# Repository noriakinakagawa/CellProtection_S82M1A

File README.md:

# CellProtection_S82M1A
1セル用バッテリー保護IC S-82M1Aテスト基板のKiCAD 6.0データ。

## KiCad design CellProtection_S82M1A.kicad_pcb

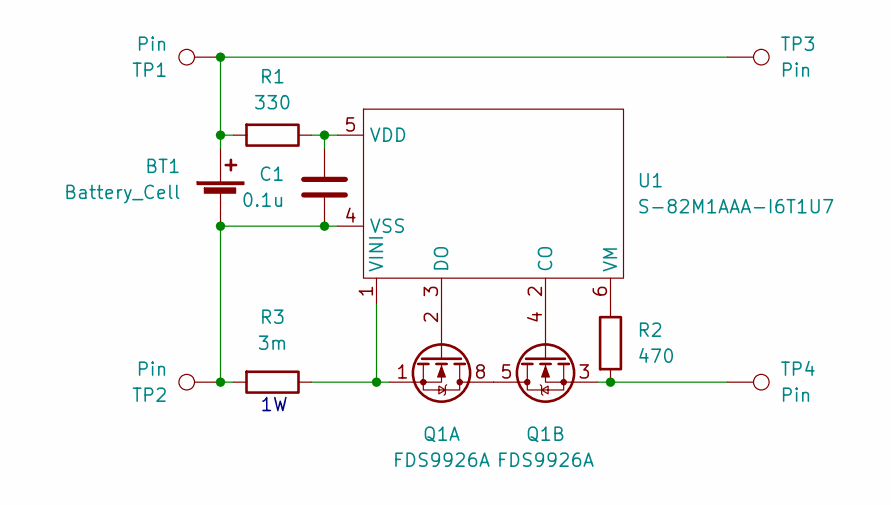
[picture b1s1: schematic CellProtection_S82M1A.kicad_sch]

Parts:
BT1: Battery_Cell; 1043
C1: 0.1u; C_0603_1608Metric_Pad1.08x0.95mm_HandSolder
Q1: FDS9926A; SOIC-8_3.9x4.9mm_P1.27mm
R1: 330; R_0603_1608Metric_Pad0.98x0.95mm_HandSolder
R2: 470; R_0603_1608Metric_Pad0.98x0.95mm_HandSolder
R3: 3m; R_1210_3225Metric_Pad1.30x2.65mm_HandSolder
TP1, TP2, TP3, TP4: Pin; TestPoint_THTPad_1.5x1.5mm_Drill0.7mm
U1: S-82M1AAA-I6T1U7; S-82M1A

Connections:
unnamed: BT1.1 (+), R1.2, TP1.1, TP3.1
unnamed: BT1.2 (-), C1.2, R3.2, TP2.1, U1.4 (VSS)
unnamed: C1.1, R1.1, U1.5 (VDD)
unnamed: Q1.1 (S1), R3.1, U1.1 (VINI)
unnamed: Q1.2 (G1), U1.3 (DO)
unnamed: Q1.3 (S2), R2.2, TP4.1
unnamed: Q1.4 (G2), U1.2 (CO)
unnamed: Q1.5 (D2), Q1.6 (D2), Q1.7 (D1), Q1.8 (D1)
unnamed: R2.1, U1.6 (VM)

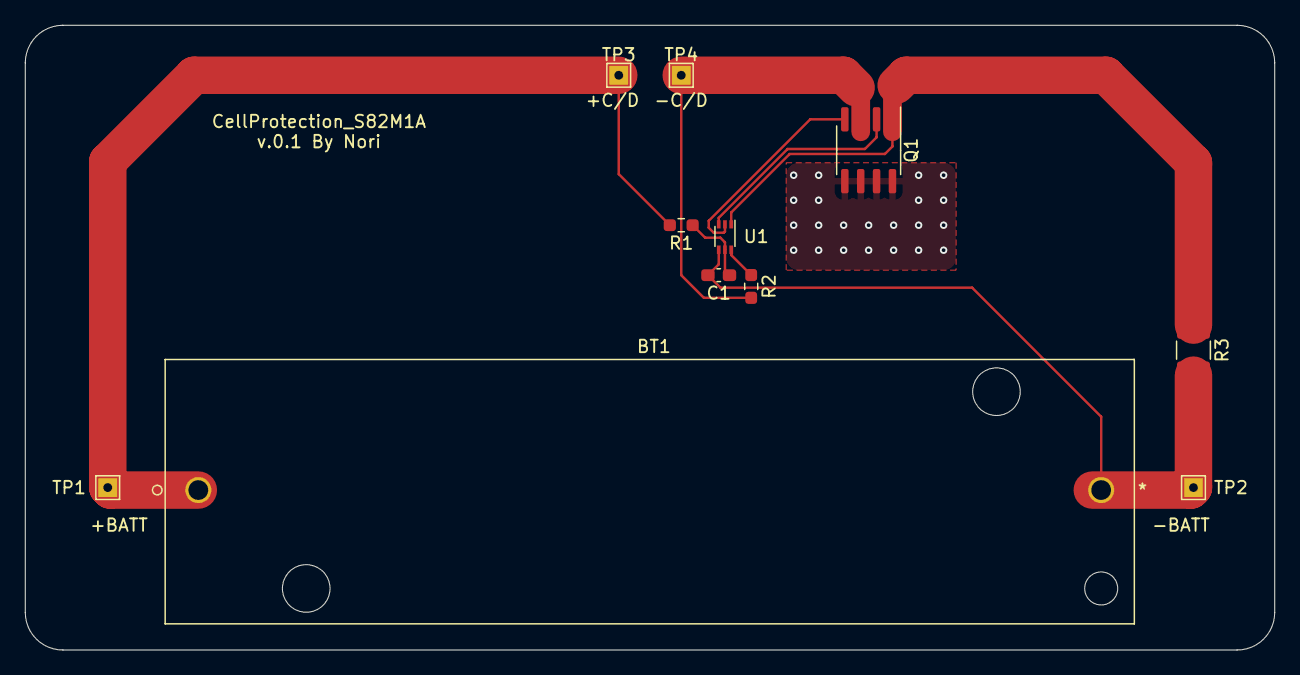
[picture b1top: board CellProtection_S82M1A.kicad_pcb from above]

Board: 2 copper layers, 100.0 x 50.0 mm, 11 parts (0 on the bottom side), 9 nets.

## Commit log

2022-08-25 Add files
2022-08-25 Update image
